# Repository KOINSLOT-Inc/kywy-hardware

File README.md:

<p align='center'>
  
  &nbsp;
  
  &nbsp;
  <a href="https://kywy.io/"><img alt="Website" src="https://img.shields.io/badge/KYWY.io-AAAAAA?style=for-the-badge&logo=data%3Aimage%2Fpng%3Bbase64%2CiVBORw0KGgoAAAANSUhEUgAAACQAAAAkCAYAAADhAJiYAAAACXBIWXMAAAAnAAAAJwEqCZFPAAAAAXNSR0IArs4c6QAAAARnQU1BAACxjwv8YQUAAAKwSURBVHgBtViNdeIwDBZ9N0A2aDa4bHDpBMcIuQ2yAd6guQngJoCbIHQC2gkCE8AGqvTivApXiuMA33t6hliSP0v%2BUbKARCBiQU1J8ouEf2deGBeSo5f%2FJPvFYnGEe4NIZCQ1SYvpaEmqqWMtJpBZUvNKkgddJ5I99FG5%2BGccKY7as6J%2FJHmZHTEflW0w247Ecd8E%2B4Jk420kVpAKMsoDR%2BeUsCv%2BXEBqO2VSFpnpxml%2BD1G%2FPk3SyMEdoSyDdcxg8ygywTiSVG0pVZOZ305IZoLXZ64pDQqdpuDXwAGv8aroFfh9Z%2FH%2FUtEb0IZOZHQqY1Yt6sgD0p2h5xSfjegv1eiAgRFChdDZGjpqWrBP3YBGC101lxC1K7Qxxe95eFALw3wGoRL7VFloYAR4vVxKfrDzfw4Rw9oY8OxFQwcR4HXa6h%2FQX4SMU6CYU8Pbn9sjyR%2FoL1N5ug79GtjmBSKgy%2FZCY508j58gZucCQptgtq0yuwptOJgI%2FFoO%2Bye4nrFEGfwvIA3PMANPI31h%2Fj8gDRUGh%2BEUMCFZXEnwmvkH%2Fdp64wH4IfY7Kvdr7DeMY42plQJ%2BXQe7iN7S2E182mrXhbn2FN%2BD30Yu3nPEqDUGHA7GEm3UI37lGVZzyt59XzYn5%2BBTTdt3T81fQ2eF9qFbit%2F78GByhtHoSS10wgJPoo347bSHnMvMMNwZA%2BWB3ljqikBXpmttOXEGoaUy%2B8bQdQqZTiG%2FsSYWRimHBwNjFWoQpfgbwW1kZCHXmQEIQv2Quhq%2FV5VVzEBWfXd5Jxsh46YYZXhdzNshTSMTnvQuxVh7r1%2FPIebXZhv4cjAHqG%2FftZ9tNmLHqdE%2B33CESrgF3vkGdXR%2B0EEOaJezDd5z5wpiHU4Hk3MpRKIfrAxyJfQVJEsuuoaPV3xh8%2Be8d0jEJ3i2%2BwETXUzkAAAAAElFTkSuQmCC&link=kywy.io" /></a>
  &nbsp;
  
</p>
<br />

# Kywy-Micro
 A handheld device for gaming
 
This repo contains all of the files you need to build a kywy pcb and 3d printed case

buy a kywy at [kywy.io](https://kywy.io)

Find our C++ and Rust libraries here: https://github.com/KOINSLOT-Inc

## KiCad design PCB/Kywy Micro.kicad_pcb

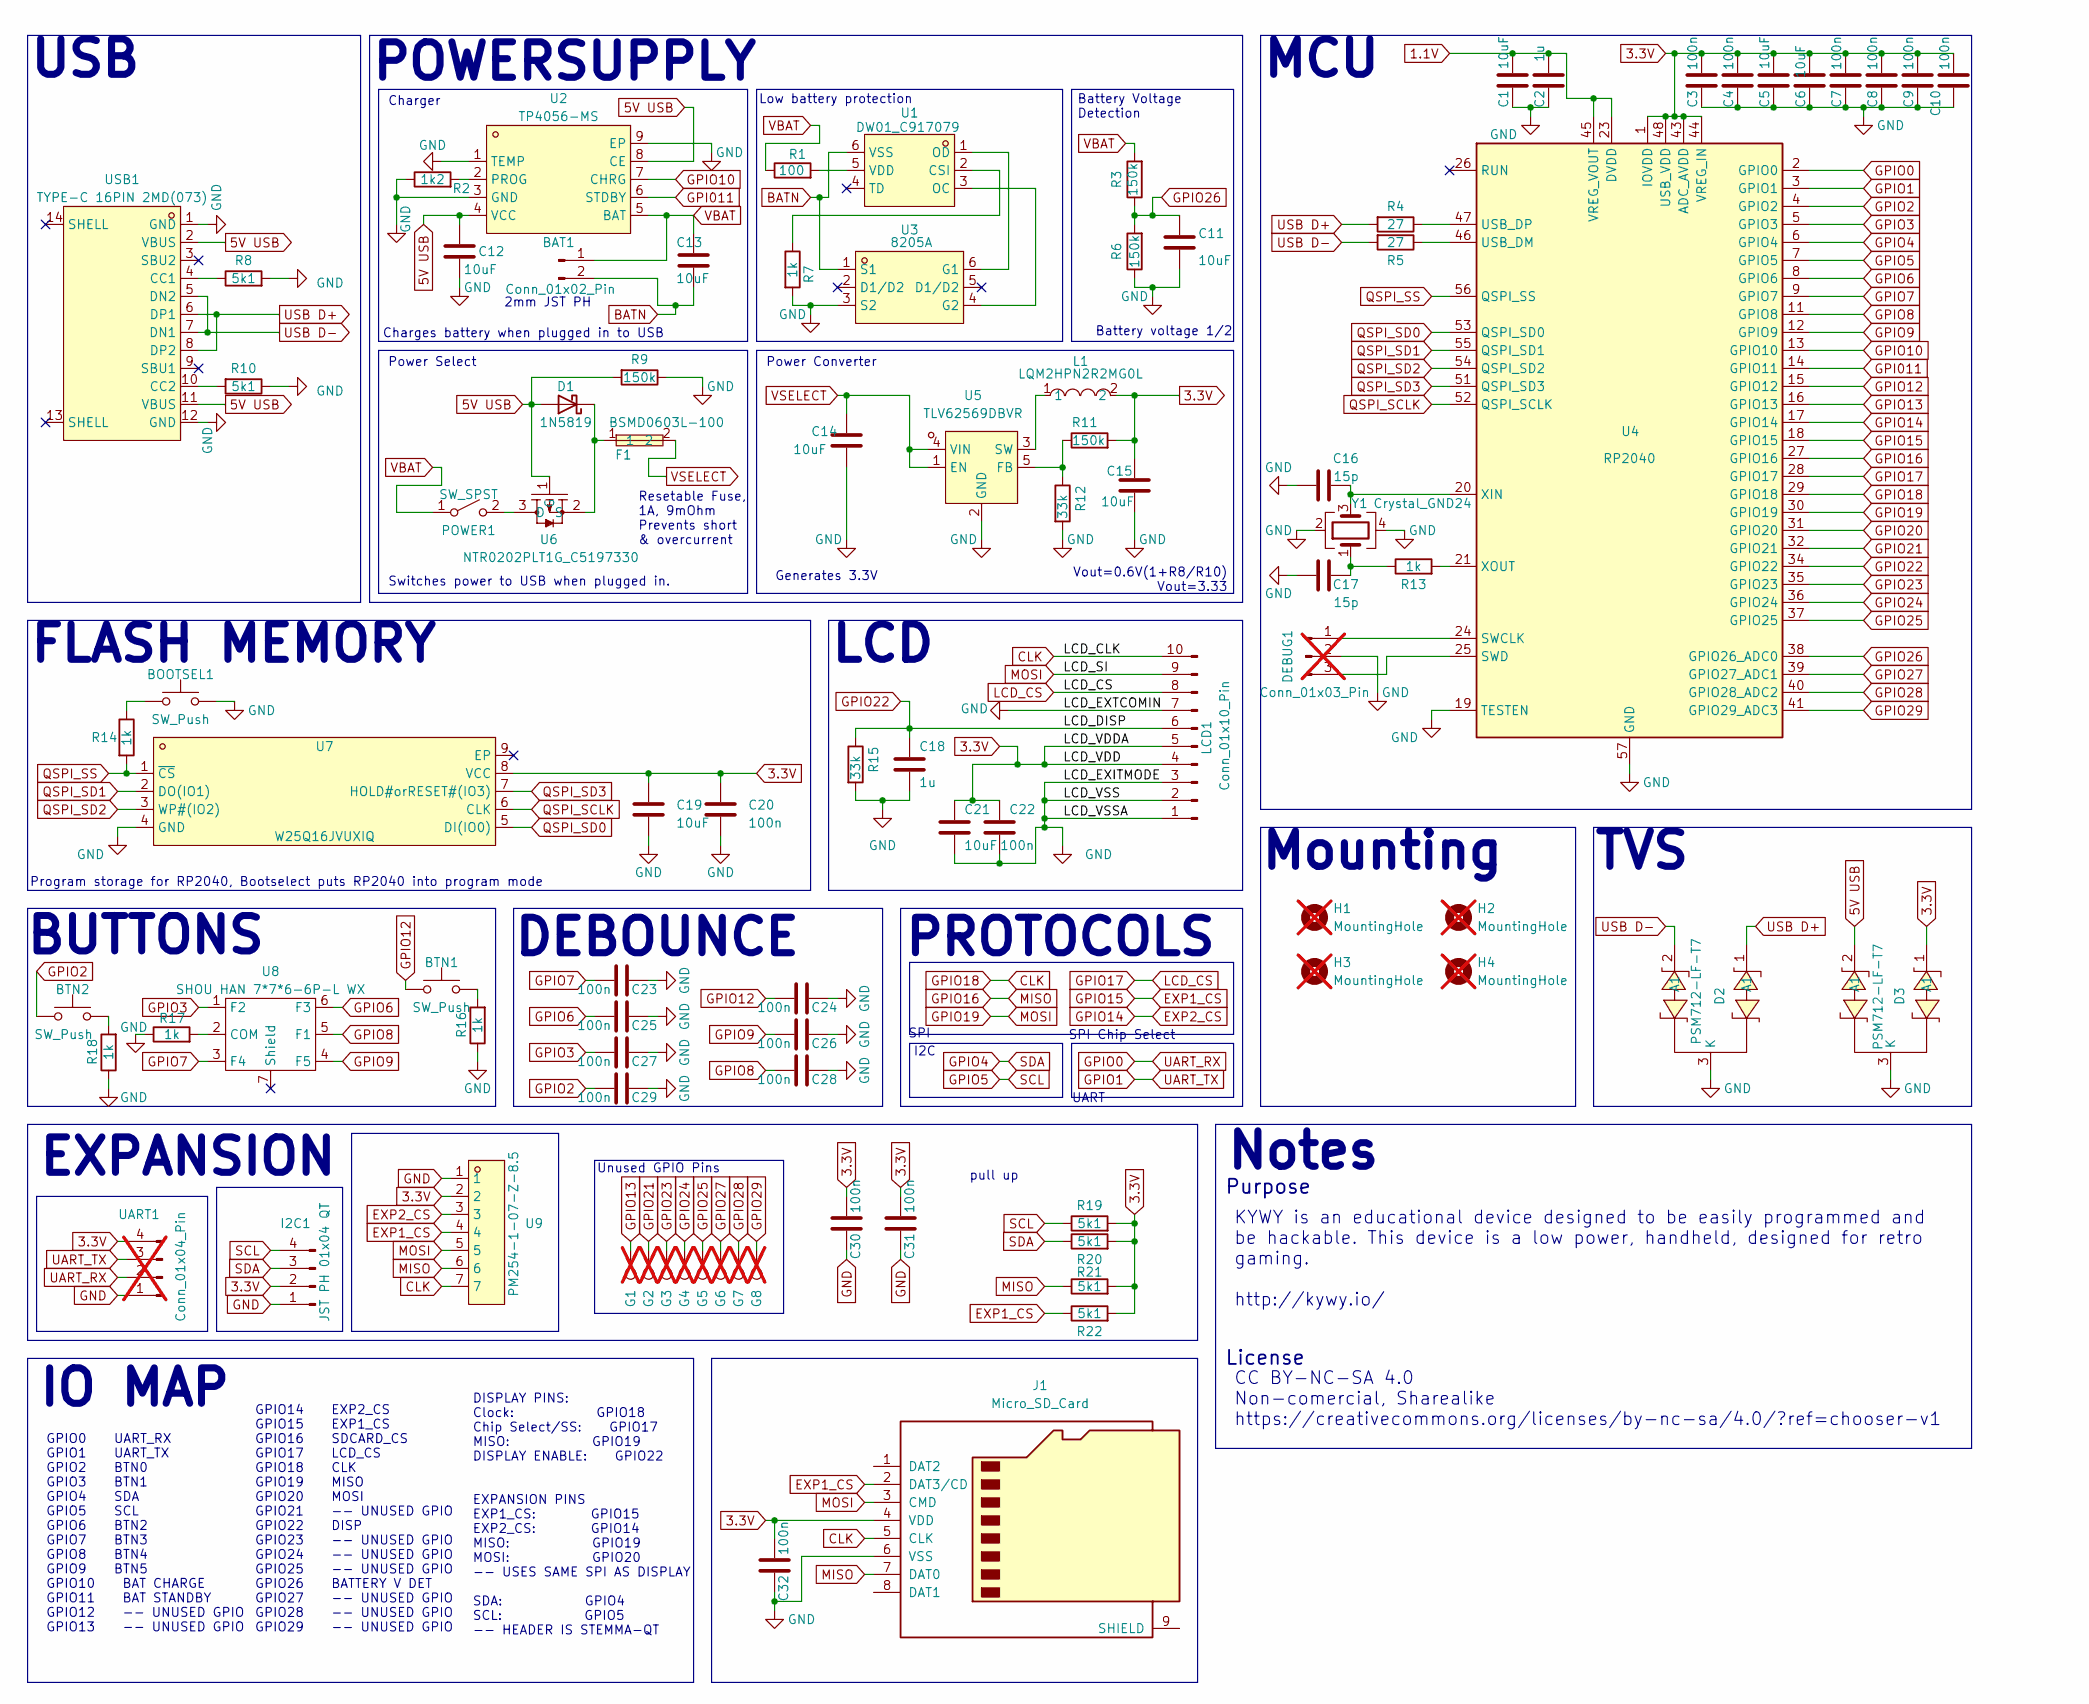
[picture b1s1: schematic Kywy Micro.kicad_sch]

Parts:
BAT1: Conn_01x02_Pin; CONN-TH_2P-P2.00_HX-2.0MM-2P-ZZ; JLCPCB Part #（optional） C5368724
BOOTSEL1: SW_Push; SW-SMD_L3.9-W3.0-P4.45; JLCPCB Part #（optional） C720477
BTN1, BTN2: SW_Push; SW-SMD_L3.9-W3.0-P4.45; JLCPCB Part #（optional） C720477
C1, C5, C6, C11, C12, C13, C14, C15, C19, C21: 10uF; C_0402_1005Metric; JLCPCB Part #（optional） C15525
C2, C18: 1u; C_0402_1005Metric; JLCPCB Part #（optional） C52923
C3, C4, C7, C8, C9, C10, C20, C22, C23, C24, C25, C26, C27, C28, C29, C30, C31, C32: 100n; C_0402_1005Metric; JLCPCB Part #（optional） C1525
C16, C17: 15p; C_0402_1005Metric; JLCPCB Part #（optional） C1548
D1: 1N5819; SOD-323_L1.8-W1.3-LS2.5-RD; JLCPCB Part #（optional） C191023
D2, D3: PSM712-LF-T7; SOT-23-3_L3.0-W1.7-P0.95-LS2.9-BR; LCSC Part C32677
DEBUG1: Conn_01x03_Pin; PinHeader_1x03_P2.54mm_Vertical; JLCPCB Part #（optional） DNP; not fitted
F1: BSMD0603L-100; F0603; JLCPCB Part #（optional） C2757929
G1, G2, G3, G4, G5, G6, G7, G8: TestPoint; Small Test Pad; JLCPCB Part #（optional） DNP; not fitted
H1, H2, H3, H4: MountingHole; MountingHole_2.2mm_M2; JLCPCB Part #（optional） DNP; not fitted
I2C1: JST PH 01x04 QT; CONN-SMD_4P-P1.00_MEGASTAR_ZX-SH1.0-4PWT; JLCPCB Part #（optional） C7430446
J1: Micro_SD_Card; TF-SMD_TF-123-ARP9H15; JLCPCB Part #（optional） C2982547
L1: LQM2HPN2R2MG0L; L1008; LCSC Part C86092
LCD1: Conn_01x10_Pin; FPC-SMD_P0.5-10P_FGS-XJ-H2.0; JLCPCB Part #（optional） C262659
POWER1: SW_SPST; SW-SMD_3P-P1.50_L2.7-W6.6; JLCPCB Part #（optional） C963206
R1: 100; R_0402_1005Metric; JLCPCB Part #（optional） C144045
R2: 1k2; R_0402_1005Metric; JLCPCB Part #（optional） C25862
R3, R6, R9, R11: 150k; R_0402_1005Metric; JLCPCB Part #（optional） C25755
R4, R5: 27; R_0402_1005Metric; JLCPCB Part #（optional） C25100
R7, R13, R14, R16, R17, R18: 1k; R_0402_1005Metric; JLCPCB Part #（optional） C11702
R8, R10, R19, R20, R21, R22: 5k1; R_0402_1005Metric; JLCPCB Part #（optional） C25905
R12, R15: 33k; R_0402_1005Metric; JLCPCB Part #（optional） C25779
U1: DW01_C917079; SOT-23-6_L2.9-W1.6-P0.95-LS2.8-BL; LCSC Part C917079
U2: TP4056-MS; SOP-8_L4.9-W3.9-P1.27-LS6.0-TL-EP; JLCPCB Part #（optional） C7473158
U3: 8205A; SOT-23-6_L2.9-W1.6-P0.95-LS2.8-BR; LCSC Part C2762931
U4: RP2040; QFN-56-1EP_7x7mm_P0.4mm_EP3.2x3.2mm; JLCPCB Part #（optional） C2040
U5: TLV62569DBVR; SOT-23-5_L3.0-W1.7-P0.95-LS2.8-BR; LCSC Part C141836
U6: NTR0202PLT1G_C5197330; SOT-23_L2.9-W1.3-P1.90-LS2.4-BR; JLCPCB Part #（optional） C5224173
U7: W25Q16JVUXIQ; USON-8_L3.0-W2.0-P0.50-BL-EP; JLCPCB Part #（optional） C2843335
U8: SHOU HAN 7*7*6-6P-L WX; SW-SMD_6P-L7.0-W7.0-P1.40-LS7.4; JLCPCB Part #（optional） C2858288
U9: PM254-1-07-Z-8.5; HDR-TH_7P-P2.54-V-F; LCSC Part C2897370
UART1: Conn_01x04_Pin; PinHeader_1x04_P2.54mm_Vertical; JLCPCB Part #（optional） DNP; not fitted
USB1: TYPE-C 16PIN 2MD(073); USB-C-SMD_TYPE-C-6PIN-2MD-073; JLCPCB Part #（optional） C2765186
Y1: Crystal_GND24; CRYSTAL-SMD_4P-L3.2-W2.5-BL; JLCPCB Part #（optional） C9002

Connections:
1.1V: C1.2, C2.2, U4.23 (DVDD), U4.45 (VREG_VOUT), U4.50 (DVDD)
3.3V: C3.2, C4.2, C5.2, C6.2, C7.2, C8.2, C9.2, C10.2, C15.1, C19.1, C20.1, C21.1, C22.1, C30.2, C31.2, C32.2, D3.1 (A1), I2C1.2, J1.4 (VDD), L1.2, LCD1.4, LCD1.5, R11.2, R19.2, R20.2, R21.2, R22.2, U4.1 (IOVDD), U4.10 (IOVDD), U4.22 (IOVDD), U4.33 (IOVDD), U4.42 (IOVDD), U4.43 (ADC_AVDD), U4.44 (VREG_IN), U4.48 (USB_VDD), U4.49 (IOVDD), U7.8 (VCC), U9.2, UART1.4
5V USB: C12.1, D1.2 (A), D3.2 (A1), R9.2, U2.4 (VCC), U2.8 (CE), U6.1 (G), USB1.2 (VBUS), USB1.11 (VBUS)
BATN: BAT1.2, C13.2, U1.6 (VSS), U3.1 (S1)
CLK: J1.5 (CLK), LCD1.10, U4.29 (GPIO18), U9.7
EXP1_CS: J1.2 (DAT3/CD), R22.1, U4.18 (GPIO15), U9.4
EXP2_CS: U4.17 (GPIO14), U9.3
GND: BOOTSEL1.2, C1.1, C2.1, C3.1, C4.1, C5.1, C6.1, C7.1, C8.1, C9.1, C10.1, C11.2, C12.2, C14.2, C15.2, C16.1, C17.1, C18.2, C19.2, C20.2, C21.2, C22.2, C23.1, C24.1, C25.1, C26.1, C27.1, C28.1, C29.1, C30.1, C31.1, C32.1, D2.3 (K), D3.3 (K), DEBUG1.2, I2C1.1, J1.6 (VSS), LCD1.1, LCD1.2, LCD1.3, LCD1.7, R2.1, R6.1, R7.2, R8.2, R9.1, R10.1, R12.2, R15.2, R16.1, R17.1, R18.1, U2.1 (TEMP), U2.3 (GND), U2.9 (EP), U3.3 (S2), U4.19 (TESTEN), U4.57 (GND), U5.2 (GND), U7.4 (GND), U9.1, UART1.1, USB1.1 (GND), USB1.12 (GND), Y1.2, Y1.4
GPI011: U2.6 (STDBY), U4.14 (GPIO11)
GPIO0: U4.2 (GPIO0), UART1.2
GPIO1: U4.3 (GPIO1), UART1.3
GPIO2: BTN2.1, C29.2, U4.4 (GPIO2)
GPIO3: C27.2, U4.5 (GPIO3), U8.1 (F2)
GPIO4: I2C1.3, R20.1, U4.6 (GPIO4)
GPIO5: I2C1.4, R19.1, U4.7 (GPIO5)
GPIO6: C25.2, U4.8 (GPIO6), U8.6 (F3)
GPIO7: C23.2, U4.9 (GPIO7), U8.3 (F4)
GPIO8: C28.2, U4.11 (GPIO8), U8.5 (F1)
GPIO9: C26.2, U4.12 (GPIO9), U8.4 (F5)
GPIO10: U2.7 (CHRG), U4.13 (GPIO10)
GPIO12: BTN1.1, C24.2, U4.15 (GPIO12)
GPIO13: G1.1, U4.16 (GPIO13)
GPIO16: J1.7 (DAT0), R21.1, U4.27 (GPIO16), U9.6
GPIO17: LCD1.8, U4.28 (GPIO17)
GPIO19: J1.3 (CMD), LCD1.9, U4.30 (GPIO19), U9.5
GPIO20: U4.31 (GPIO20)
GPIO21: G2.1, U4.32 (GPIO21)
GPIO22: C18.1, LCD1.6, R15.1, U4.34 (GPIO22)
GPIO23: G3.1, U4.35 (GPIO23)
GPIO24: G4.1, U4.36 (GPIO24)
GPIO25: G5.1, U4.37 (GPIO25)
GPIO26: C11.1, R3.1, R6.2, U4.38 (GPIO26_ADC0)
GPIO27: G6.1, U4.39 (GPIO27_ADC1)
GPIO28: G7.1, U4.40 (GPIO28_ADC2)
GPIO29: G8.1, U4.41 (GPIO29_ADC3)
unnamed: BOOTSEL1.1, R14.1
unnamed: BTN1.2, R16.2
unnamed: BTN2.2, R18.2
unnamed: C17.2, R13.1, Y1.1
unnamed: D1.1 (K), F1.1, U6.2 (S)
unnamed: DEBUG1.1, U4.24 (SWCLK)
unnamed: DEBUG1.3, U4.25 (SWD)
unnamed: POWER1.2 (B), U6.3 (D)
unnamed: R7.1, U1.2 (CSI)
unnamed: U1.3 (OC), U3.4 (G2)
unnamed: U1.1 (OD), U3.6 (G1)
unnamed: R1.2, U1.5 (VDD)
unnamed: R2.2, U2.2 (PROG)
unnamed: R5.1, U4.46 (USB_DM)
unnamed: R4.1, U4.47 (USB_DP)
unnamed: C16.2, U4.20 (XIN), Y1.3
unnamed: R13.2, U4.21 (XOUT)
unnamed: R11.1, R12.1, U5.5 (FB)
unnamed: L1.1, U5.3 (SW)
unnamed: R17.2, U8.2 (COM)
unnamed: R8.1, USB1.4 (CC1)
unnamed: R10.2, USB1.10 (CC2)
QSPI_SCLK: U4.52 (QSPI_SCLK), U7.6 (CLK)
QSPI_SD0: U4.53 (QSPI_SD0), U7.5 (DI(IO0))
QSPI_SD1: U4.55 (QSPI_SD1), U7.2 (DO(IO1))
QSPI_SD2: U4.54 (QSPI_SD2), U7.3 (WP#(IO2))
QSPI_SD3: U4.51 (QSPI_SD3), U7.7 (HOLD#orRESET#(IO3))
QSPI_SS: R14.2, U4.56 (QSPI_SS), U7.1 (~CS)
USB D+: D2.1 (A1), R4.2, USB1.6 (DP1), USB1.8 (DP2)
USB D-: D2.2 (A1), R5.2, USB1.5 (DN2), USB1.7 (DN1)
VBAT: BAT1.1, C13.1, POWER1.1 (A), R1.1, R3.2, U2.5 (BAT)
VSELECT: C14.1, F1.2, U5.1 (EN), U5.4 (VIN)

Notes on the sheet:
Power Select
Notes
SPI Chip Select
Low battery protection
Battery voltage 1/2
EXPANSION
Charger
DISPLAY PINS: Clock: GPIO18 Chip Select/SS: GPIO17 MISO: GPIO19 DISPLAY ENABLE: GPIO22 EXPANSION PINS EXP1_CS: GPIO15 EXP2_CS: GPIO14 MISO: GPIO19 MOSI: GPIO20 -- USES SAME SPI AS DISPLAY SDA: GPIO4 SCL: GPIO5 -- HEADER IS STEMMA-QT
Vout=0.6V(1+R8/R10) Vout=3.33
pull up
CC BY-NC-SA 4.0 Non-comercial, Sharealike https://creativecommons.org/licenses/by-nc-sa/4.0/?ref=chooser-v1
PROTOCOLS
2mm JST PH
License
Battery Voltage Detection
Generates 3.3V
I2C
Switches power to USB when plugged in.
SPI
FLASH MEMORY
UART
TVS
Program storage for RP2040, Bootselect puts RP2040 into program mode
Unused GPIO Pins
IO MAP
MCU
GPIO0 UART_RX GPIO1 UART_TX GPIO2 BTN0 GPIO3 BTN1 GPIO4 SDA GPIO5 SCL GPIO6 BTN2 GPIO7 BTN3 GPIO8 BTN4 GPIO9 BTN5 GPIO10 BAT CHARGE GPIO11 BAT STANDBY GPIO12 -- UNUSED GPIO GPIO13 -- UNUSED GPIO
Mounting
KYWY is an educational device designed to be easily programmed and be hackable. This device is a low power, handheld, designed for retro gaming. http://kywy.io/
Resetable Fuse, 1A, 9mOhm Prevents short & overcurrent
GPIO14 EXP2_CS GPIO15 EXP1_CS GPIO16 SDCARD_CS GPIO17 LCD_CS GPIO18 CLK GPIO19 MISO GPIO20 MOSI GPIO21 -- UNUSED GPIO GPIO22 DISP GPIO23 -- UNUSED GPIO GPIO24 -- UNUSED GPIO GPIO25 -- UNUSED GPIO GPIO26 BATTERY V DET GPIO27 -- UNUSED GPIO GPIO28 -- UNUSED GPIO GPIO29 -- UNUSED GPIO
Purpose
POWERSUPPLY
DEBOUNCE
Power Converter
BUTTONS
LCD
Charges battery when plugged in to USB
USB

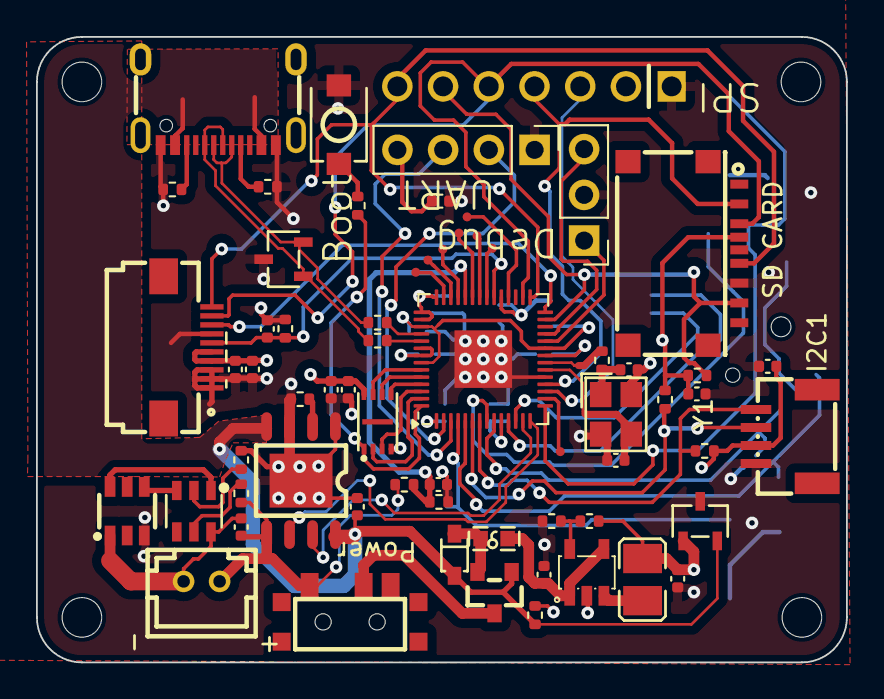
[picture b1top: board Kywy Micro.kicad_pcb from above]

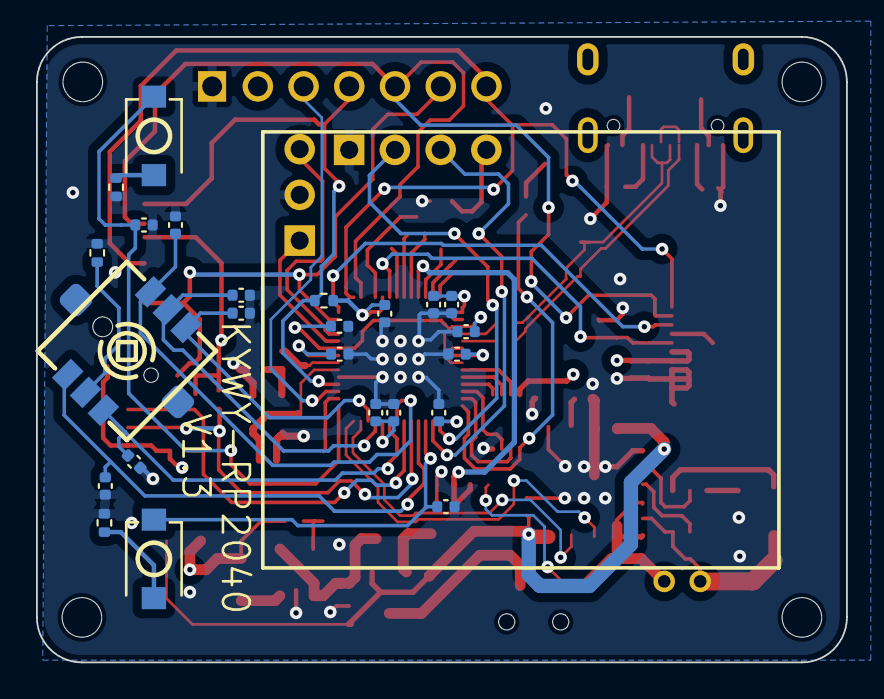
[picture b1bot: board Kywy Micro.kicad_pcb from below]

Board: 4 copper layers, 45.0 x 34.8 mm, 92 parts (24 on the bottom side), 66 nets.

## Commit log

2025-04-18 init
2025-04-18 Create LICENSE
